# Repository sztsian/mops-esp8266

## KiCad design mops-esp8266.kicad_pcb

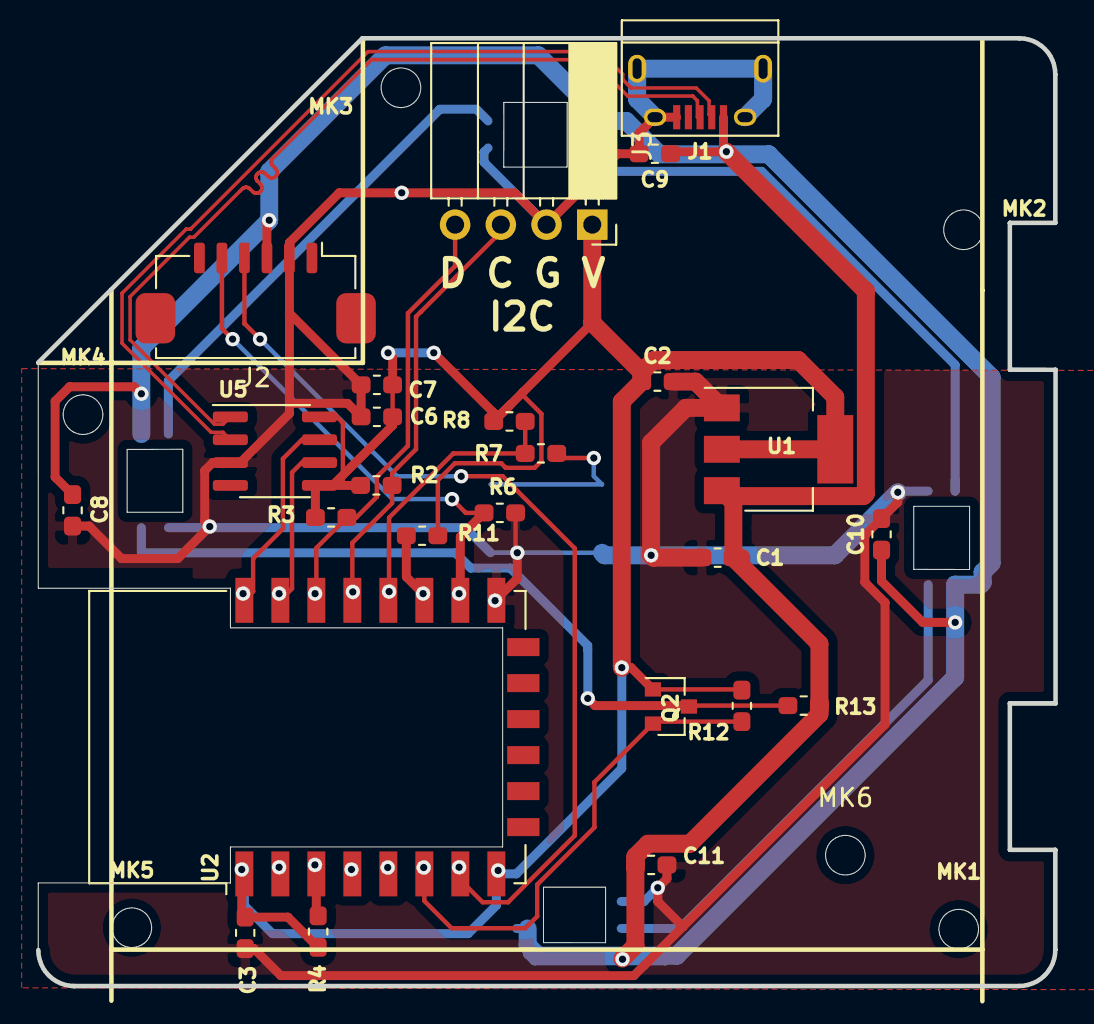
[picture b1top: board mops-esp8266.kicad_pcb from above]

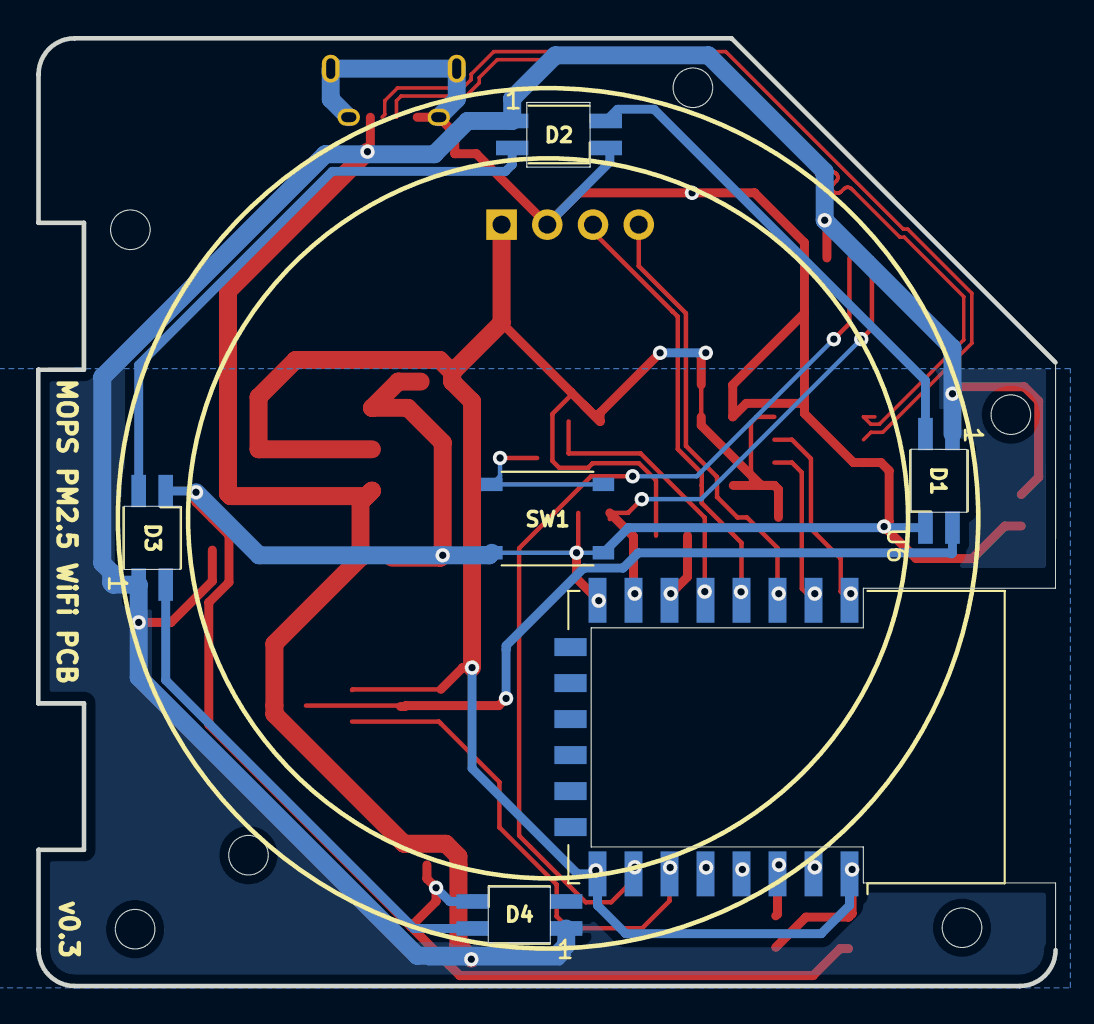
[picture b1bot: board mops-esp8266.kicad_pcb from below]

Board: 2 copper layers, 56.5 x 52.7 mm, 37 parts (6 on the bottom side), 23 nets.

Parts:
C1: 10uF; C_0603_1608Metric_Pad1.05x0.95mm_HandSolder
C2, C3, C6, C7, C8, C9, C10, C11: 100nF; C_0603_1608Metric_Pad1.05x0.95mm_HandSolder
D1, D2, D3, D4: WS2812B; LED_DY-S352818_RGBC_6812-2T
J1: USB_B_Micro; USB_Micro-B_Connector
J2: PMS7003; 1.25mm_connector_Vertical-based-on-molex-502382-1x06
J3: Ext_I2C; PinSocket_1x04_P2.54mm_Horizontal
MK1, MK2, MK3, MK4, MK5: M2; MountingHole_2.2mm_M2
MK6: M1; MountingHole_2.2mm_M2
Q2: 2N7002; SOT-23
R2, R3, R4, R6, R8, R11: 10k; R_0603_1608Metric_Pad1.05x0.95mm_HandSolder
R7: 470; R_0603_1608Metric_Pad1.05x0.95mm_HandSolder
R12, R13: 1k; R_0603_1608Metric_Pad1.05x0.95mm_HandSolder
SW1: SW_Flash; switch_4x4x1.5_real-5x5x1.5
U1: AP1117-33; SOT-223-3_TabPin2
U2, U6: ESP-12F; ESP-12E
U5: CH330N; SOIC-8_3.9x4.9mm_P1.27mm

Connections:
3V3_MCU: C2.1, C3.1, C6.1, C7.1, J3.1, Q2.1, R2.2, R3.2, R4.2, R8.1, R11.1, R12.2, U1.2, U2.1, U2.8, U5.5, U5.8, U6.1, U6.8
A0: U2.2, U6.2
EN: R4.1, U2.3, U6.3
GND: C1.2, C2.2, C3.2, C6.2, C7.2, C8.2, C9.2, C10.2, C11.2, D1.3, D2.3, D3.3, D4.3, J1.5, J1.6, J2.2, J3.2, R6.1, SW1.2, U1.1, U2.15, U5.3, U6.15
GPIO0: R7.2, R8.2, U2.18, U6.18
GPIO2: R11.2, U2.17, U6.17
GPIO4: J3.3, R2.1, U2.19, U6.19
GPIO5: J3.4, R3.1, U2.20, U6.20
GPIO12: Q2.2, R12.1, U2.6, U6.6
GPIO13: J2.4, U2.7, U6.7
GPIO14: U2.5, U6.5
GPIO15: J2.5, R6.2, U2.16, U6.16
GPIO16: U2.4, U6.4
IF_RXD: U2.22, U5.7, U6.22
IF_TXD: U2.21, U5.6, U6.21
unnamed: D1.2, D2.4
unnamed: D1.4, Q2.3, R13.1
unnamed: D2.2, D3.4
unnamed: D3.2, D4.4
unnamed: R7.1, SW1.1
USB-D+: J1.3, U5.1
USB-D-: J1.2, U5.2
VBUS: C1.1, C8.1, C9.1, C10.1, C11.1, D1.1, D2.1, D3.1, D4.1, J1.1, J2.3, R13.2, U1.3

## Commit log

2020-10-18 Add the initial version
2020-10-18 Add some used symbol/footprint
2020-10-26 WIP: Add a place to solde ESP12F on the back
2020-12-06 Upload v0.2. Still not working.
    Size of PCB is too large on the buttom size
    ESP modules should move right a bit
    D2 should move down a bit
    Temperature sensor can be removed as the self heating affects it too
    much
2020-12-06 Update to v0.3
    Fixes board size and position in various places
    Removed temperature sensor
